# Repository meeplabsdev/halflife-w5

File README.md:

# Orange Pi Zero 3 HAT
|||
|---|---|

This is a HAT for the Orange Pi Zero 3, which adds some extra features!

# What it is
This project was created for week 5 of [halflife](https://halflife.hackclub.com/)! I designed the schematic and PCB using [KiCad](https://www.kicad.org/), as a hat for the [Orange Pi Zero 3](http://www.orangepi.org/orangepiwiki/index.php/Orange_Pi_Zero_3). It adds the following features:
- New USB C power input, with better filtering and control (limited to 5v, maybe PD/QC in the future)
- Connections for the power, display controller and touch controller of [this](https://www.aliexpress.com/item/1005008698035882.html) display
- Headphone amplifier and 3.5mm jack for the LINEOUT exposed by the 13 pins
- Separate LoRa board that can be used via USB or connected to the HAT internally over SPI/UART
- 1 button and 1 rotary encoder on the front face, 5 buttons on the back face, all controls are along the side
- Support for connecting and using the 5 buttons from the IO board of the aforementioned display as extra inputs
- Almost entirely through-hole components, exceptions are the headphone amplifier, 4 JST connectors, large electrolytic caps and the mosfets
- Also its jam packed

# Hardware
Schematic:

PCB:
|||
|---|---|

# Cost
This is a rough outline of the cost, see [`BOM.csv`](bom.csv) for more details.

| Part | Cost |
| --- | --- |
| [Main HAT](https://jlcpcb.com/) | $4.00 |
| [LoRa board](https://jlcpcb.com/) | $8.00 |
| [LoRa board stencil](https://jlcpcb.com/) | $7.22 |
| [LoRa antenna](https://www.aliexpress.com/item/1005008297942095.html) | $4.75 |
| [All board components](https://lcsc.com/) | $53.77 |
| **Total + Shipping** | **$99.70** |

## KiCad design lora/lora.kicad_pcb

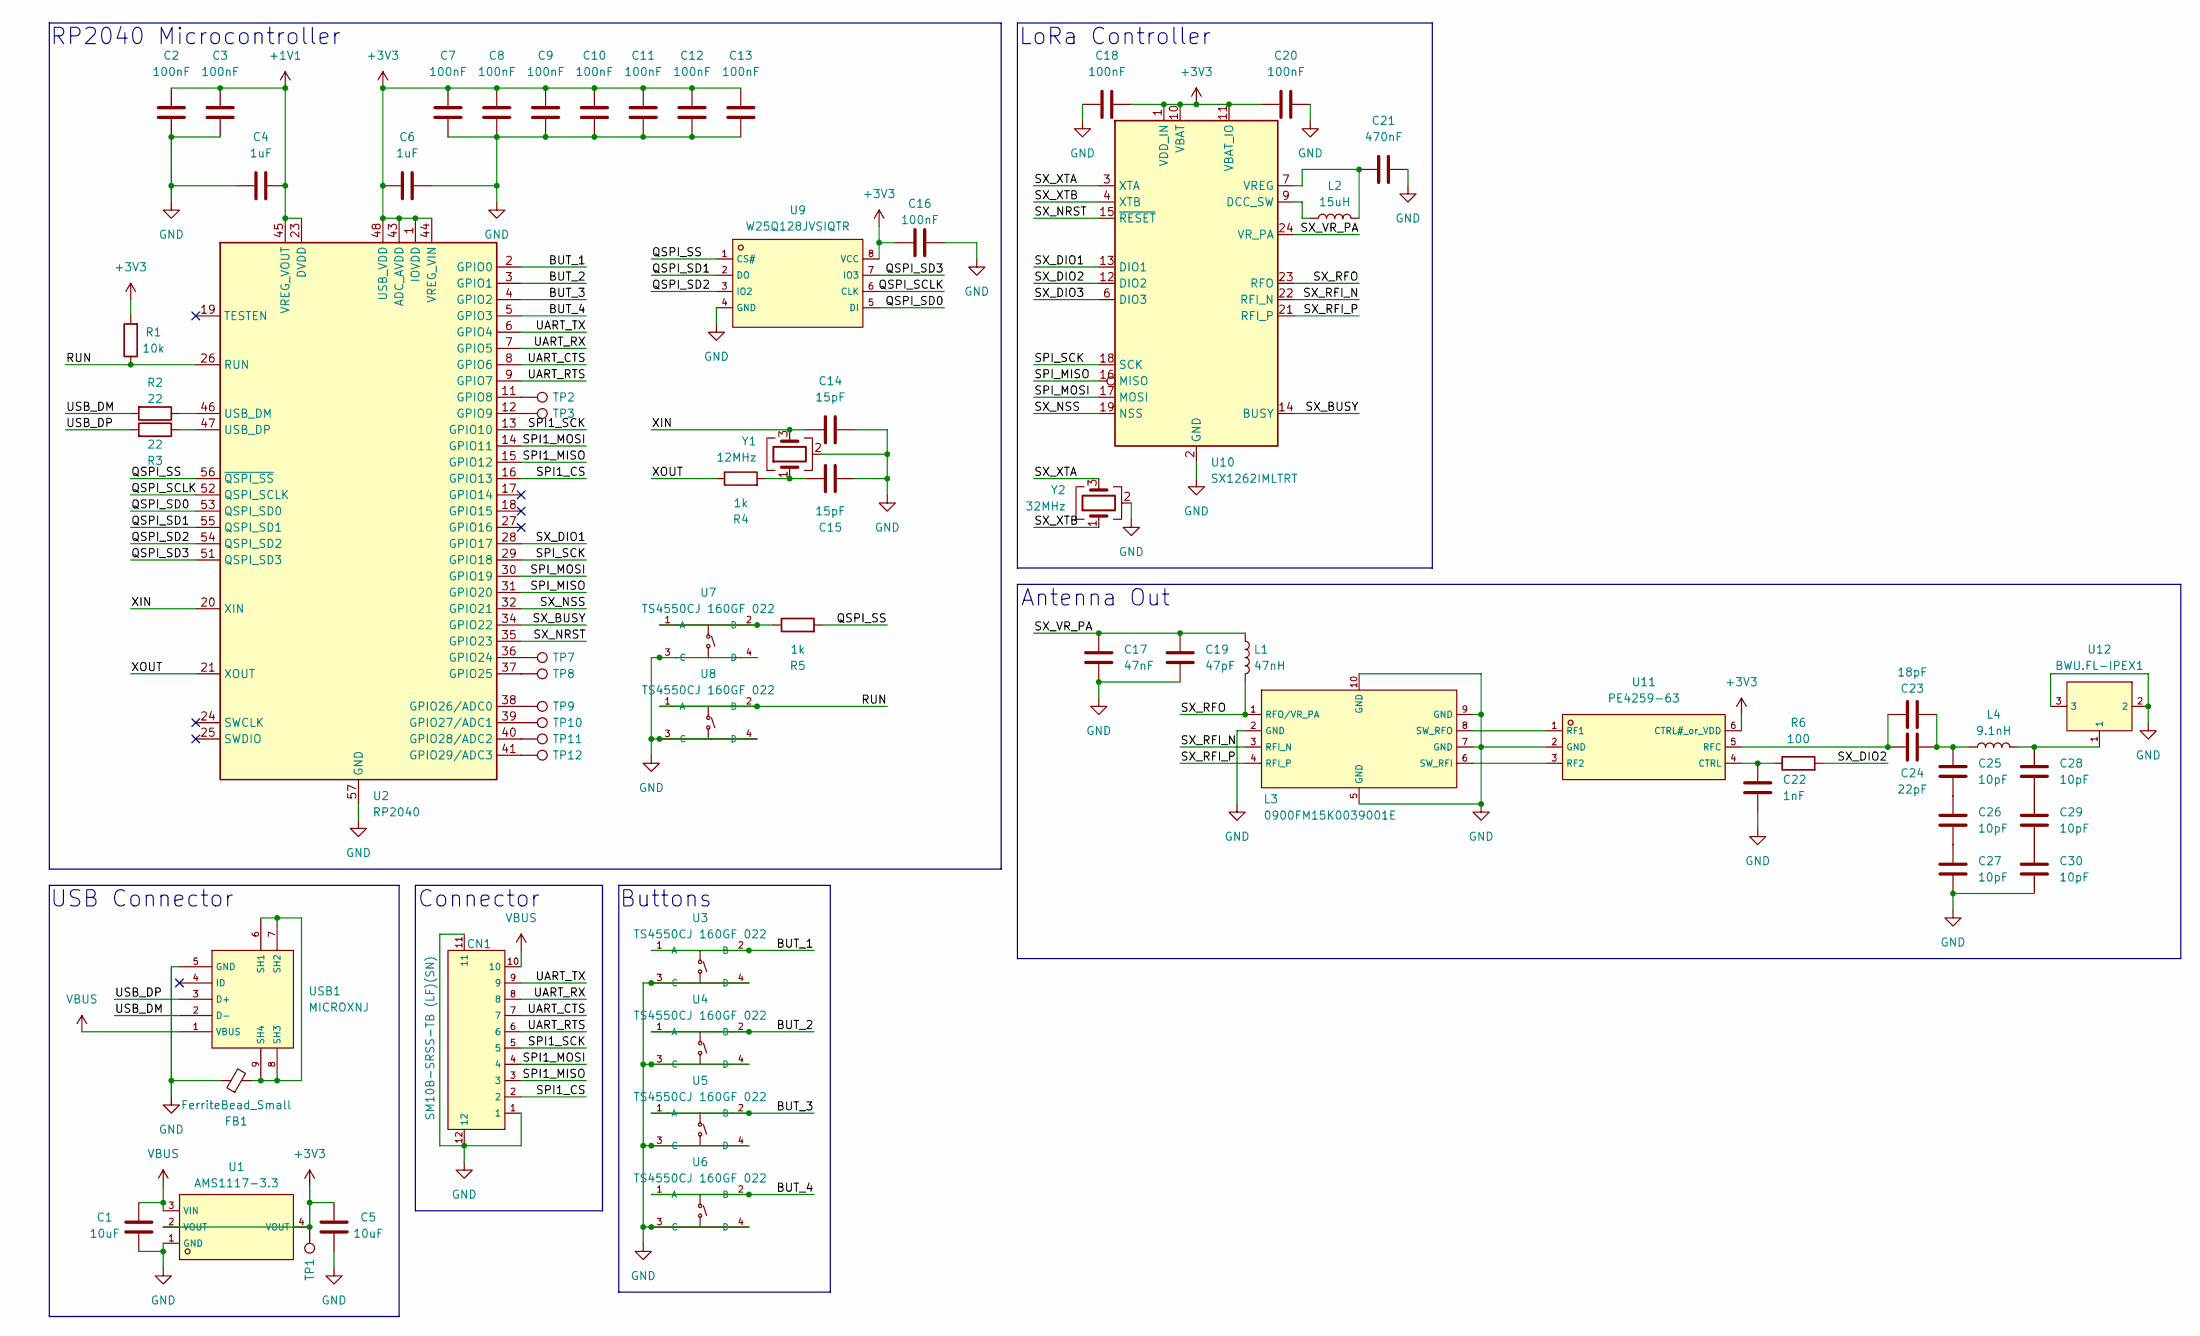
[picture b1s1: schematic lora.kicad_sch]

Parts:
C1, C5: 10uF; C_0402_1005Metric; LCSC C15525
C2, C3, C7, C8, C9, C10, C11, C12, C13, C16, C18, C20: 100nF; C_0402_1005Metric; LCSC C1525
C4, C6: 1uF; C_0402_1005Metric; LCSC C52923
C14, C15: 15pF; C_0402_1005Metric; LCSC C1548
C17: 47nF; C_0603_1608Metric; LCSC C1622
C19: 47pF; C_0402_1005Metric; LCSC C1567
C21: 470nF; C_0603_1608Metric; LCSC C1623
C22: 1nF; C_0402_1005Metric; LCSC C76947
C23: 18pF; C_0402_1005Metric; LCSC C1549
C24: 22pF; C_0402_1005Metric; LCSC C1555
C25, C26, C27, C28, C29, C30: 10pF; C_0402_1005Metric; LCSC C32949
CN1: SM10B-SRSS-TB (LF)(SN); C160409_CONN-SMD_10P-P1_00_SM10B-SRSS-TB-LF-SN; LCSC C160409
FB1: FerriteBead_Small; L_0402_1005Metric; LCSC C85815
L1: 47nH; L_0402_1005Metric; LCSC C27151
L2: 15uH; L_0603_1608Metric; LCSC C57838
L3: 0900FM15K0039001E; C7434807_FILTER-SMD_10P-L2_0-W1_3-BL; LCSC C7434807
L4: 9.1nH; L_0402_1005Metric; LCSC C113059
R1: 10k; R_0402_1005Metric; LCSC C60490
R2, R3: 22; R_0402_1005Metric; LCSC C114765
R4, R5: 1k; R_0402_1005Metric; LCSC C11702
R6: 100; R_0402_1005Metric; LCSC C25076
TP1, TP2, TP3, TP7, TP8, TP9, TP10, TP11, TP12: TestPoint; TestPoint_Pad_1.0x1.0mm
U1: AMS1117-3.3; C6186_SOT-223-3_L6_5-W3_4-P2_30-LS7_0-BR; LCSC C6186
U2: RP2040; QFN-56-1EP_7x7mm_P0.4mm_EP3.2x3.2mm; LCSC C2040
U3, U4, U5, U6, U7, U8: TS4550CJ 160GF 022; C5369123_SW-TH_4P-L4_5-W4_5-P3_00-LS5_0; LCSC C5369123
U9: W25Q128JVSIQTR; C97521_SOIC-8_L5_3-W5_3-P1_27-LS8_0-BL; LCSC C97521
U10: SX1262IMLTRT; QFN-24-1EP_4x4mm_P0.5mm_EP2.6x2.6mm; LCSC C191341
U11: PE4259-63; C470892_SC-70-6_L2_2-W1_3-P0_65-LS2_1-BL; LCSC C470892
U12: BWU.FL-IPEX1; C5137195_IPEX-SMD_BWIPX-1-001E; LCSC C5137195
USB1: MICROXNJ; C404969_MICRO-USB-SMD_MICROXNJ_1; LCSC C404969
Y1: 12MHz; Crystal_SMD_3225-4Pin_3.2x2.5mm; LCSC C9002
Y2: 32MHz; Crystal_SMD_2016-4Pin_2.0x1.6mm; LCSC C2965582

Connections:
+1V1: C2.1, C3.1, C4.1, U2.23 (DVDD), U2.45 (VREG_VOUT), U2.50 (DVDD)
+3V3: C5.1, C6.2, C7.1, C8.1, C9.1, C10.1, C11.1, C12.1, C13.1, C16.2, C18.2, C20.1, R1.2, TP1.1 (1_1), U1.2 (VOUT), U1.4 (VOUT), U2.1 (IOVDD), U2.10 (IOVDD), U2.22 (IOVDD), U2.33 (IOVDD), U2.42 (IOVDD), U2.43 (ADC_AVDD), U2.44 (VREG_VIN), U2.48 (USB_VDD), U2.49 (IOVDD), U9.8 (VCC), U10.1 (VDD_IN), U10.10 (VBAT), U10.11 (VBAT_IO), U11.6 (CTRL#_or_VDD)
/BUT_1: U2.2 (GPIO0), U3.1 (A), U3.2 (B)
/BUT_2: U2.3 (GPIO1), U4.1 (A), U4.2 (B)
/BUT_3: U2.4 (GPIO2), U5.1 (A), U5.2 (B)
/BUT_4: U2.5 (GPIO3), U6.1 (A), U6.2 (B)
/QSPI_SCLK: U2.52 (QSPI_SCLK), U9.6 (CLK)
/QSPI_SD0: U2.53 (QSPI_SD0), U9.5 (DI)
/QSPI_SD1: U2.55 (QSPI_SD1), U9.2 (DO)
/QSPI_SD2: U2.54 (QSPI_SD2), U9.3 (IO2)
/QSPI_SD3: U2.51 (QSPI_SD3), U9.7 (IO3)
/QSPI_SS: R5.2, U2.56 (~QSPI_SS), U9.1 (CS#)
/RUN: R1.1, U2.26 (RUN), U8.1 (A), U8.2 (B)
/SPI1_CS: CN1.2, U2.16 (GPIO13)
/SPI1_MISO: CN1.3, U2.15 (GPIO12)
/SPI1_MOSI: CN1.4, U2.14 (GPIO11)
/SPI1_SCK: CN1.5, U2.13 (GPIO10)
/SPI_MISO: U2.31 (GPIO20), U10.16 (MISO)
/SPI_MOSI: U2.30 (GPIO19), U10.17 (MOSI)
/SPI_SCK: U2.29 (GPIO18), U10.18 (SCK)
/SX_BUSY: U2.34 (GPIO22), U10.14 (BUSY)
/SX_DIO1: U2.28 (GPIO17), U10.13 (DIO1)
/SX_DIO2: R6.2, U10.12 (DIO2)
/SX_DIO3: U10.6 (DIO3)
/SX_NRST: U2.35 (GPIO23), U10.15 (~RESET)
/SX_NSS: U2.32 (GPIO21), U10.19 (NSS)
/SX_RFI_N: L3.3 (RFI_N), U10.22 (RFI_N)
/SX_RFI_P: L3.4 (RFI_P), U10.21 (RFI_P)
/SX_RFO: L1.2, L3.1 (RFO/VR_PA), U10.23 (RFO)
/SX_VR_PA: C17.1, C19.1, L1.1, U10.24 (VR_PA)
/SX_XTA: U10.3 (XTA), Y2.3
/SX_XTB: U10.4 (XTB), Y2.1
/UART_CTS: CN1.7, U2.8 (GPIO6)
/UART_RTS: CN1.6, U2.9 (GPIO7)
/UART_RX: CN1.8, U2.7 (GPIO5)
/UART_TX: CN1.9, U2.6 (GPIO4)
/USB_DM: R2.2, USB1.2 (D-)
/USB_DP: R3.2, USB1.3 (D+)
/XIN: C14.2, U2.20 (XIN), Y1.3
/XOUT: R4.1, U2.21 (XOUT)
GND: C1.2, C2.2, C3.2, C4.2, C5.2, C6.1, C7.2, C8.2, C9.2, C10.2, C11.2, C12.2, C13.2, C14.1, C15.1, C16.1, C17.2, C18.1, C19.2, C20.2, C21.2, C22.1, C27.1, C30.1, CN1.1, CN1.11, CN1.12, FB1.1, L3.2 (GND), L3.5 (GND), L3.7 (GND), L3.9 (GND), L3.10 (GND), U1.1 (GND), U2.57 (GND), U3.3 (C), U3.4 (D), U4.3 (C), U4.4 (D), U5.3 (C), U5.4 (D), U6.3 (C), U6.4 (D), U7.3 (C), U7.4 (D), U8.3 (C), U8.4 (D), U9.4 (GND), U10.2 (GND), U10.5 (GND), U10.8 (GND), U10.20 (GND), U10.25 (GND), U11.2 (GND), U12.2, U12.3, USB1.5 (GND), Y1.2 (G), Y1.4 (G), Y2.2 (G), Y2.4 (G)
unnamed: C15.2, R4.2, Y1.1
unnamed: C23.2, C24.2, C25.2, L4.1
unnamed: C25.1, C26.2
unnamed: C26.1, C27.2
unnamed: C28.1, C29.2
unnamed: C28.2, L4.2, U12.1
unnamed: C29.1, C30.2
unnamed: L3.6 (SW_RFI), U11.3 (RF2)
unnamed: L3.8 (SW_RFO), U11.1 (RF1)
unnamed: TP2.1 (1_1), U2.11 (GPIO8)
unnamed: TP3.1 (1_1), U2.12 (GPIO9)
unnamed: TP7.1 (1_1), U2.36 (GPIO24)
unnamed: TP8.1 (1_1), U2.37 (GPIO25)
unnamed: TP9.1 (1_1), U2.38 (GPIO26/ADC0)
unnamed: TP10.1 (1_1), U2.39 (GPIO27/ADC1)
unnamed: TP11.1 (1_1), U2.40 (GPIO28/ADC2)
unnamed: TP12.1 (1_1), U2.41 (GPIO29/ADC3)
unnamed: R2.1, U2.46 (USB_DM)
unnamed: R3.1, U2.47 (USB_DP)
unnamed: R5.1, U7.1 (A), U7.2 (B)
unnamed: L2.1, U10.9 (DCC_SW)
unnamed: C21.1, L2.2, U10.7 (VREG)
unnamed: C22.2, R6.1, U11.4 (CTRL)
unnamed: C23.1, C24.1, U11.5 (RFC)
unnamed: FB1.2, USB1.6 (SH1), USB1.7 (SH2), USB1.8 (SH3), USB1.9 (SH4)
VBUS: C1.1, CN1.10, U1.3 (VIN), USB1.1 (VBUS)

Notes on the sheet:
LoRa Controller
Buttons
Antenna Out
Connector
USB Connector
RP2040 Microcontroller

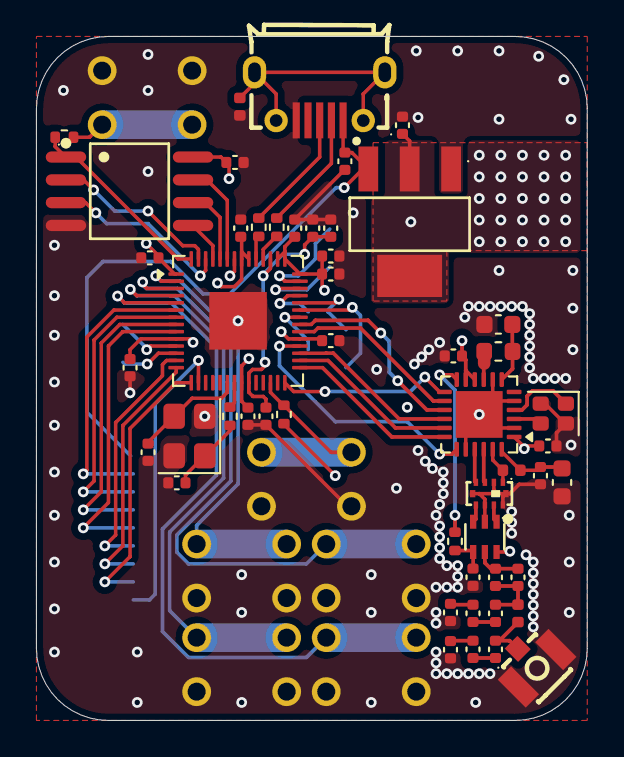
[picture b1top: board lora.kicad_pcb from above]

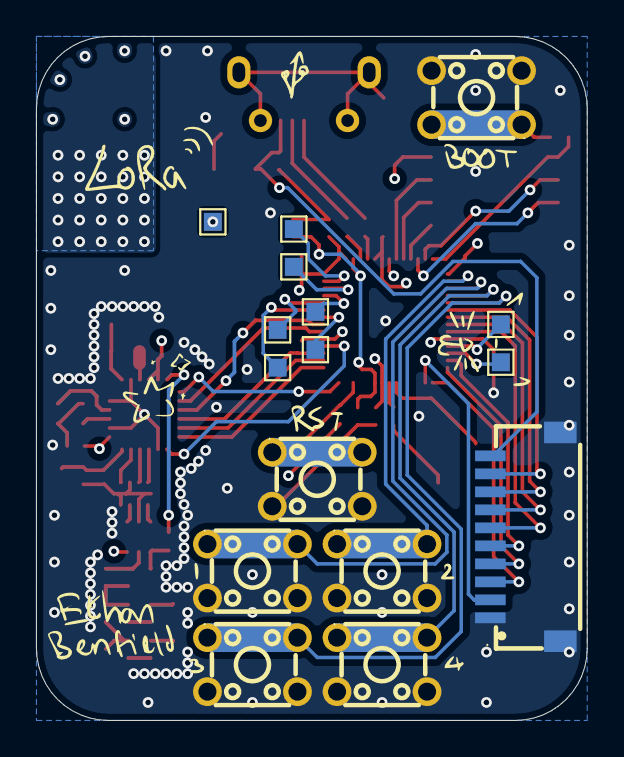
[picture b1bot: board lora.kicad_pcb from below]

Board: 4 copper layers, 30.6 x 38.0 mm, 66 parts (16 on the bottom side), 66 nets.

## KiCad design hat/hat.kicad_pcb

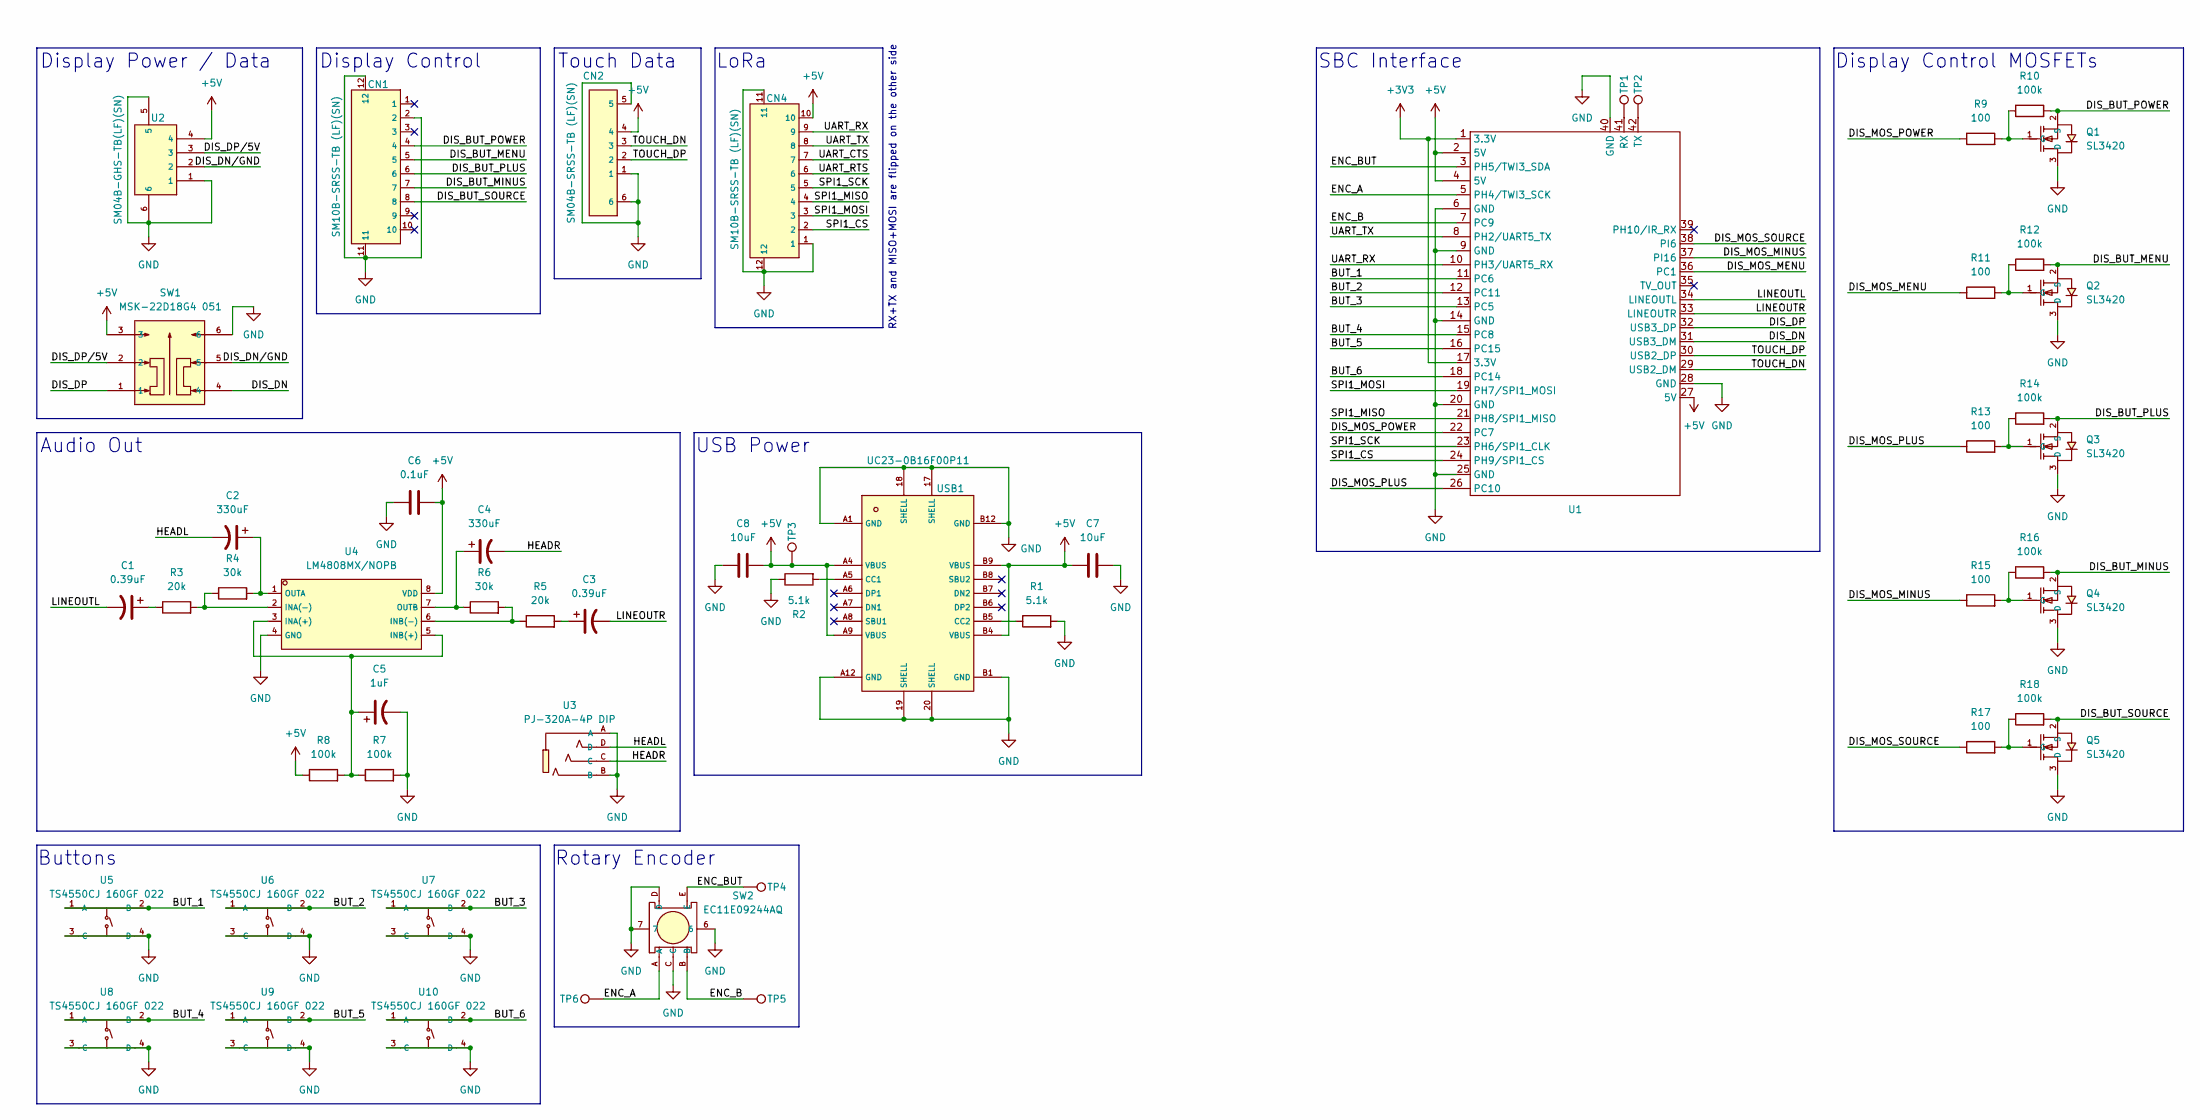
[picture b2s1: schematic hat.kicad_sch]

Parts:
C1, C3: 0.39uF; CP_Elec_4x5.4; LCSC C22387960
C2, C4: 330uF; CP_Elec_8x10.5; LCSC C335985
C5: 1uF; CP_Elec_4x5.4; LCSC C72491
C6: 0.1uF; C_Disc_D7.5mm_W4.4mm_P5.00mm; LCSC C52140108
C7, C8: 10uF; C_Disc_D5.1mm_W3.2mm_P5.00mm; LCSC C2761740
CN1, CN4: SM10B-SRSS-TB (LF)(SN); C160409_CONN-SMD_10P-P1_00_SM10B-SRSS-TB-LF-SN; LCSC C160409
CN2: SM04B-SRSS-TB (LF)(SN); C160404_CONN-SMD_4P-P1_00_SM04B-SRSS-TB-LF-SN; LCSC C160404
Q1, Q2, Q3, Q4, Q5: SL3420; C50087708_SOT-23-3_L2_9-W1_3-P1_90-LS2_4-BR; LCSC C50087708
R1, R2: 5.1k; R_Axial_DIN0207_L6.3mm_D2.5mm_P10.16mm_Horizontal; LCSC C714010
R3, R5: 20k; R_Axial_DIN0207_L6.3mm_D2.5mm_P10.16mm_Horizontal; LCSC C119353
R4, R6: 30k; R_Axial_DIN0207_L6.3mm_D2.5mm_P10.16mm_Horizontal; LCSC C129921
R7, R8, R10, R12, R14, R16, R18: 100k; R_Axial_DIN0207_L6.3mm_D2.5mm_P10.16mm_Horizontal; LCSC C2843019
R9, R11, R13, R15, R17: 100; R_Axial_DIN0207_L6.3mm_D2.5mm_P10.16mm_Horizontal; LCSC C385440
SW1: MSK-22D18G4 051; C7507433_SW-TH_HX-MSK-22D18G4-051; LCSC C7507433
SW2: EC11E09244AQ; C470753_SW-TH_EC11XXXXXXXX; LCSC C470753
TP1, TP2, TP3, TP4, TP5, TP6: TestPoint; SolderWirePad_1x01_SMD_1.5x3mm
U1: Orange_Pi_Zero_3
U2: SM04B-GHS-TB(LF)(SN); C189895_CONN-SMD_4P-P1_25_SM04B-GHS-TB-LF-SN; LCSC C189895
U3: PJ-320A-4P DIP; C18185602_AUDIO-TH_PJ-320A-4P-DIP; LCSC C18185602
U4: LM4808MX/NOPB; C141374_SOIC-8_L4_9-W3_9-P1_27-LS6_0-BL-2; LCSC C141374
U5, U6, U7, U8, U9, U10: TS4550CJ 160GF 022; C5369123_SW-TH_4P-L4_5-W4_5-P3_00-LS5_0; LCSC C5369123
USB1: UC23-0B16F00P11; C36936564_USB-C-TH_UC23-0B16F00P11; LCSC C36936564

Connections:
+3V3: U1.1 (3.3V), U1.17 (3.3V)
+5V: C6.2, C7.1, C8.2, CN2.4, CN4.10, R8.1, SW1.3, TP3.1 (1_1), U1.2 (5V), U1.4 (5V), U1.27 (5V), U2.4, U4.8 (VDD), USB1.A4 (VBUS), USB1.A9 (VBUS), USB1.B4 (VBUS), USB1.B9 (VBUS)
/BUT_1: U1.11 (PC6), U5.1 (A), U5.2 (B)
/BUT_2: U1.12 (PC11), U6.1 (A), U6.2 (B)
/BUT_3: U1.13 (PC5), U7.1 (A), U7.2 (B)
/BUT_4: U1.15 (PC8), U8.1 (A), U8.2 (B)
/BUT_5: U1.16 (PC15), U9.1 (A), U9.2 (B)
/BUT_6: U1.18 (PC14), U10.1 (A), U10.2 (B)
/DIS_BUT_MENU: CN1.5, Q2.2 (S), R12.2
/DIS_BUT_MINUS: CN1.7, Q4.2 (S), R16.2
/DIS_BUT_PLUS: CN1.6, Q3.2 (S), R14.2
/DIS_BUT_POWER: CN1.4, Q1.2 (S), R10.2
/DIS_BUT_SOURCE: CN1.8, Q5.2 (S), R18.2
/DIS_DN: SW1.4, U1.31 (USB3_DM)
/DIS_DN/GND: SW1.5, U2.2
/DIS_DP: SW1.1, U1.32 (USB3_DP)
/DIS_DP/5V: SW1.2, U2.3
/DIS_MOS_MENU: R11.1, U1.36 (PC1)
/DIS_MOS_MINUS: R15.1, U1.37 (PI16)
/DIS_MOS_PLUS: R13.1, U1.26 (PC10)
/DIS_MOS_POWER: R9.1, U1.22 (PC7)
/DIS_MOS_SOURCE: R17.1, U1.38 (PI6)
/ENC_A: SW2.A, TP6.1 (1_1), U1.5 (PH4/TWI3_SCK)
/ENC_B: SW2.B, TP5.1 (1_1), U1.7 (PC9)
/ENC_BUT: SW2.E, TP4.1 (1_1), U1.3 (PH5/TWI3_SDA)
/HEADL: C2.2, U3.D
/HEADR: C4.2, U3.C
/LINEOUTL: C1.2, U1.34 (LINEOUTL)
/LINEOUTR: C3.2, U1.33 (LINEOUTR)
/SPI1_CS: CN4.2, U1.24 (PH9/SPI1_CS)
/SPI1_MISO: CN4.4, U1.21 (PH8/SPI1_MISO)
/SPI1_MOSI: CN4.3, U1.19 (PH7/SPI1_MOSI)
/SPI1_SCK: CN4.5, U1.23 (PH6/SPI1_CLK)
/TOUCH_DN: CN2.3, U1.29 (USB2_DM)
/TOUCH_DP: CN2.2, U1.30 (USB2_DP)
/UART_CTS: CN4.7
/UART_RTS: CN4.6
/UART_RX: CN4.9, U1.10 (PH3/UART5_RX)
/UART_TX: CN4.8, U1.8 (PH2/UART5_TX)
GND: C5.2, C6.1, C7.2, C8.1, CN1.2, CN1.11, CN1.12, CN2.1, CN2.5, CN2.6, CN4.1, CN4.11, CN4.12, Q1.3 (D), Q2.3 (D), Q3.3 (D), Q4.3 (D), Q5.3 (D), R1.2, R2.1, R7.2, SW1.6, SW2.6, SW2.7, SW2.C, SW2.D, U1.6 (GND), U1.9 (GND), U1.14 (GND), U1.20 (GND), U1.25 (GND), U1.28 (GND), U1.40 (GND), U2.1, U2.5, U2.6, U3.A, U3.B, U4.4 (GNO), U5.3 (C), U5.4 (D), U6.3 (C), U6.4 (D), U7.3 (C), U7.4 (D), U8.3 (C), U8.4 (D), U9.3 (C), U9.4 (D), U10.3 (C), U10.4 (D), USB1.17 (SHELL), USB1.18 (SHELL), USB1.19 (SHELL), USB1.20 (SHELL), USB1.A1 (GND), USB1.A12 (GND), USB1.B1 (GND), USB1.B12 (GND)
unnamed: C1.1, R3.1
unnamed: C3.1, R5.2
unnamed: Q1.1 (G), R9.2, R10.1
unnamed: Q2.1 (G), R11.2, R12.1
unnamed: Q3.1 (G), R13.2, R14.1
unnamed: Q4.1 (G), R15.2, R16.1
unnamed: Q5.1 (G), R17.2, R18.1
unnamed: TP1.1 (1_1), U1.41 (RX)
unnamed: TP2.1 (1_1), U1.42 (TX)
unnamed: C5.1, R7.1, R8.2, U4.3 (INA(+)), U4.5 (INB(+))
unnamed: R3.2, R4.1, U4.2 (INA(-))
unnamed: R5.1, R6.2, U4.6 (INB(-))
unnamed: C2.1, R4.2, U4.1 (OUTA)
unnamed: C4.1, R6.1, U4.7 (OUTB)
unnamed: R2.2, USB1.A5 (CC1)
unnamed: R1.1, USB1.B5 (CC2)

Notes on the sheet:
RX+TX and MISO+MOSI are flipped on the other side
Touch Data
LoRa
Display Control
USB Power
Audio Out
SBC Interface
Display Control MOSFETs
Buttons
Rotary Encoder
Display Power / Data

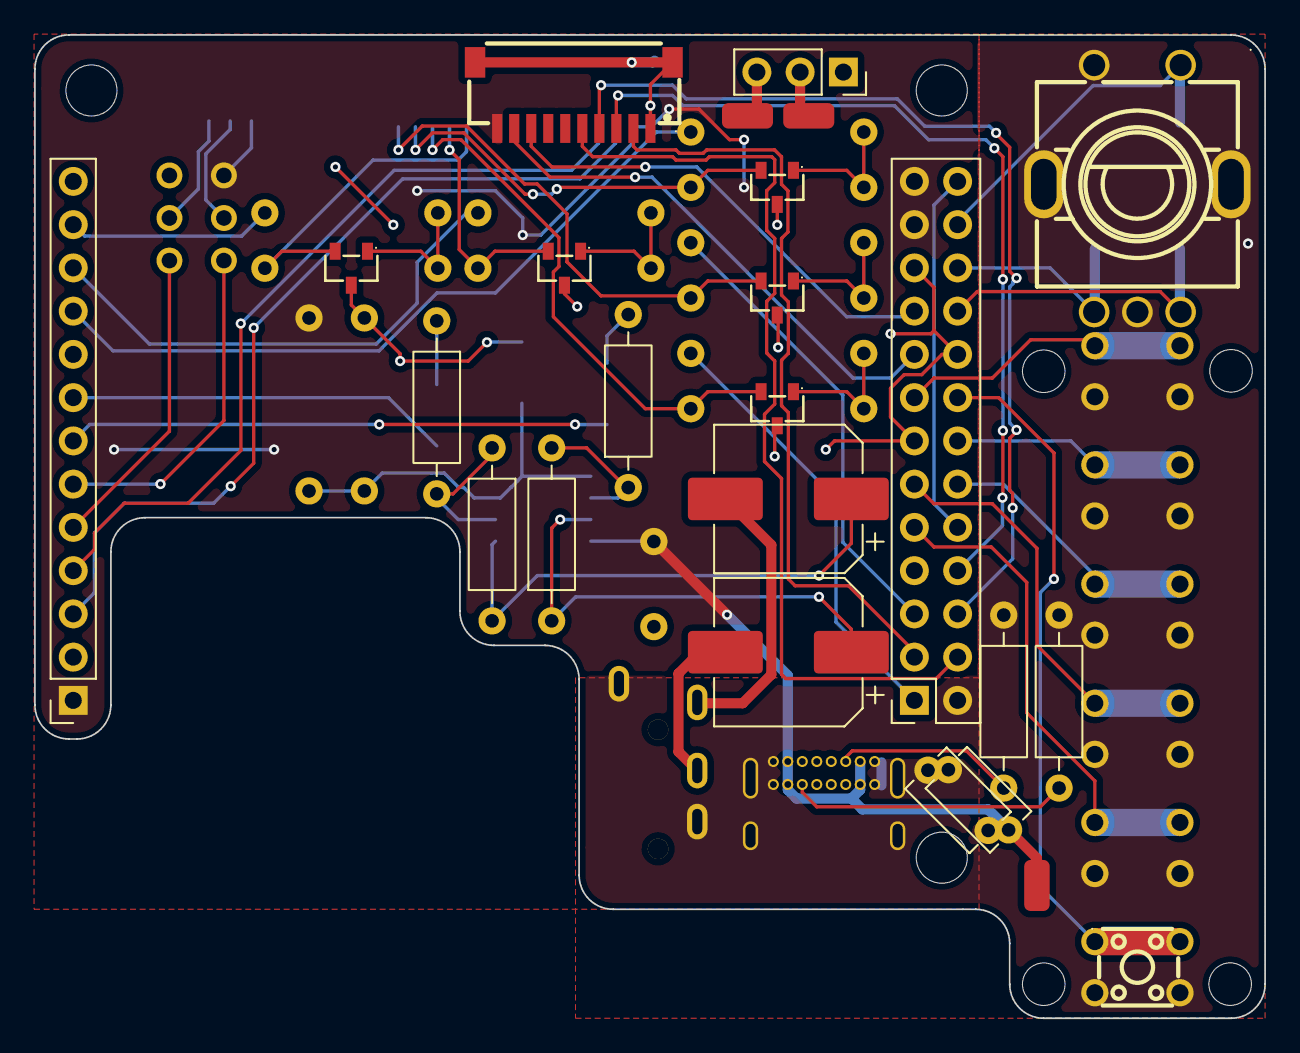
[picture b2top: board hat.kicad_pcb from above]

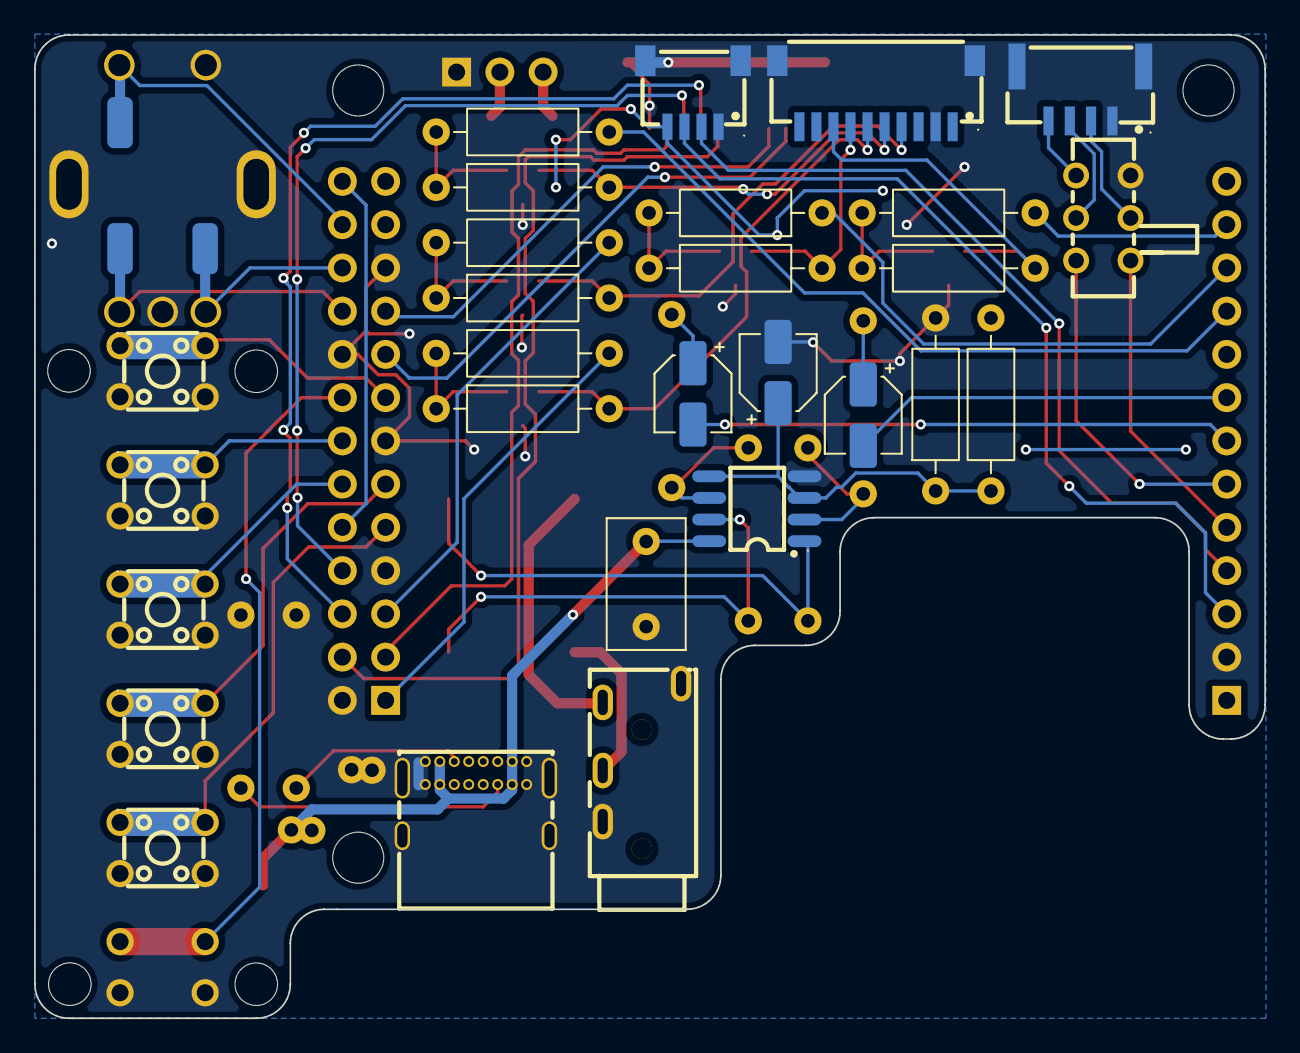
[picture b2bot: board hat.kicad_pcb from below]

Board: 2 copper layers, 72.2 x 57.8 mm, 53 parts (31 on the bottom side), 54 nets.

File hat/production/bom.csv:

Designator,Footprint,Quantity,Value,LCSC Part #
"C1, C3",CP_Elec_4x5.4,2,0.39uF,C22387960
"C2, C4",CP_Elec_8x10.5,2,330uF,C335985
C5,CP_Elec_4x5.4,1,1uF,C72491
C6,C_Disc_D7.5mm_W4.4mm_P5.00mm,1,0.1uF,C52140108
"C7, C8",C_Disc_D5.1mm_W3.2mm_P5.00mm,2,10uF,C2761740
"CN1, CN4",C160409_CONN-SMD_10P-P1_00_SM10B-SRSS-TB-LF-SN,2,SM10B-SRSS-TB (LF)(SN),C160409
CN2,C160404_CONN-SMD_4P-P1_00_SM04B-SRSS-TB-LF-SN,1,SM04B-SRSS-TB (LF)(SN),C160404
"Q1, Q2, Q3, Q4, Q5",C50087708_SOT-23-3_L2_9-W1_3-P1_90-LS2_4-BR,5,SL3420,C50087708
"R1, R2",R_Axial_DIN0207_L6.3mm_D2.5mm_P10.16mm_Horizontal,2,5.1k,C714010
"R10, R12, R14, R16, R18, R7, R8",R_Axial_DIN0207_L6.3mm_D2.5mm_P10.16mm_Horizontal,7,100k,C2843019
"R11, R13, R15, R17, R9",R_Axial_DIN0207_L6.3mm_D2.5mm_P10.16mm_Horizontal,5,100,C385440
"R3, R5",R_Axial_DIN0207_L6.3mm_D2.5mm_P10.16mm_Horizontal,2,20k,C119353
"R4, R6",R_Axial_DIN0207_L6.3mm_D2.5mm_P10.16mm_Horizontal,2,30k,C129921
SW1,C7507433_SW-TH_HX-MSK-22D18G4-051,1,MSK-22D18G4 051,C7507433
SW2,C470753_SW-TH_EC11XXXXXXXX,1,EC11E09244AQ,C470753
"TP1, TP2, TP3, TP4, TP5, TP6",SolderWirePad_1x01_SMD_1.5x3mm,6,TestPoint,
"U10, U5, U6, U7, U8, U9",C5369123_SW-TH_4P-L4_5-W4_5-P3_00-LS5_0,6,TS4550CJ 160GF 022,C5369123
U2,C189895_CONN-SMD_4P-P1_25_SM04B-GHS-TB-LF-SN,1,SM04B-GHS-TB(LF)(SN),C189895
U3,C18185602_AUDIO-TH_PJ-320A-4P-DIP,1,PJ-320A-4P DIP,C18185602
U4,C141374_SOIC-8_L4_9-W3_9-P1_27-LS6_0-BL-2,1,LM4808MX/NOPB,C141374
USB1,C36936564_USB-C-TH_UC23-0B16F00P11,1,UC23-0B16F00P11,C36936564
